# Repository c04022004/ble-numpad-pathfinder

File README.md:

# README.md

A pathfinder PCB for the upcoming Lipo-powered version of ESP32 BLE numpad. Arduino code also attached.

[Schematics PDF](./sch-export.pdf) | [Arduino Code](./arduino-freertos-code/ble_keyboard/ble_keyboard.ino) | [3D model](./3d-models/numpad-case-v10.3mf)

## Showcase

Assembled PCB  

</p>

Assembled PCB  w/ 3D print parts  

</p>

## 3D-printed Parts

The two 3D printed parts (front plate & base) are fixed to the PCB asembly with 2pcs M3x20 screws.  
The parts are designed in Fusion360, and the exported files can be found at the [3d-models/](./3d-models/) folder.

## Known Problems
- ~~USB Type-C CC pins was lay out incorrectly~~ (still testing, maybe a USB cable compat issue)
    - Reason: CC pins should be connected to `GND` with `5.1kΩ` resistor per USB Type-C definition ([link1](https://community.silabs.com/s/article/what-s-the-role-of-cc-pin-in-type-c-solution?language=en_US) [link2](https://community.silabs.com/s/article/legacy-usb-device-detection-by-type-c?language=en_US))
    - Temporary fix: not populating `R10` & `R11`, might led to inability to connect when Type-C plug is flipped
- WS2812 data line `DIN` might be affected my noise
    - Problem: Should add a `500Ω` resistor in series on `DIN` line to improve signal reliability, as per NeoPixel UberGuide
    - Temporary fix: avoid changing CPU frequency scaling on-the-fly, which may affect GPIO line conditions
- TCA8418 IC is not intended to be use with key matrix and diodes
    - Reason: originally designed for (pathfinding) swapping in diode and check the effect of ghosting
    - Temporary fix: populate diode components with `0805 0Ω` resistors
- Hotplug shoe for keyswitch is not strong enough to hold it in place
    - Reason: there is no faceplate to hold/align the keyswitches
    - Temporary fix: use 5-pin version of keyswitches for added stability, use hotglue if necessary
    - **NEW**: use a 3d printed positioning plate uploaded [here](./3d-models/)

Hopefully all issues can be fixed in the next revision to the PCB.

## Credits

I used & referenced a lot from the design from the other open-source projects.  
Here is the list of git repos:  

### KiCAD
- https://github.com/keebio/keebio-components
- https://github.com/keebio/Keebo-Parts.pretty
- https://github.com/perigoso/keyswitch-kicad-library
- https://github.com/ebastler/marbastlib
- https://github.com/AnthonyDiGirolamo/i2c-thumb-keyboard
- https://github.com/gorbachev/KiCad-SSD1306-0.91-OLED-4pin-128x32.pretty
- https://github.com/sparkfun/SparkFun-KiCad-Libraries
- https://github.com/Digi-Key/digikey-kicad-library

### Arduino/FreeRTOS
- https://github.com/kitesurfer1404/WS2812FX
- https://github.com/greiman/SSD1306Ascii
- https://github.com/adafruit/Adafruit_INA219
- https://github.com/adafruit/Adafruit_TCA8418
- https://github.com/espressif/arduino-esp32
- https://www.freertos.org/a00113.html

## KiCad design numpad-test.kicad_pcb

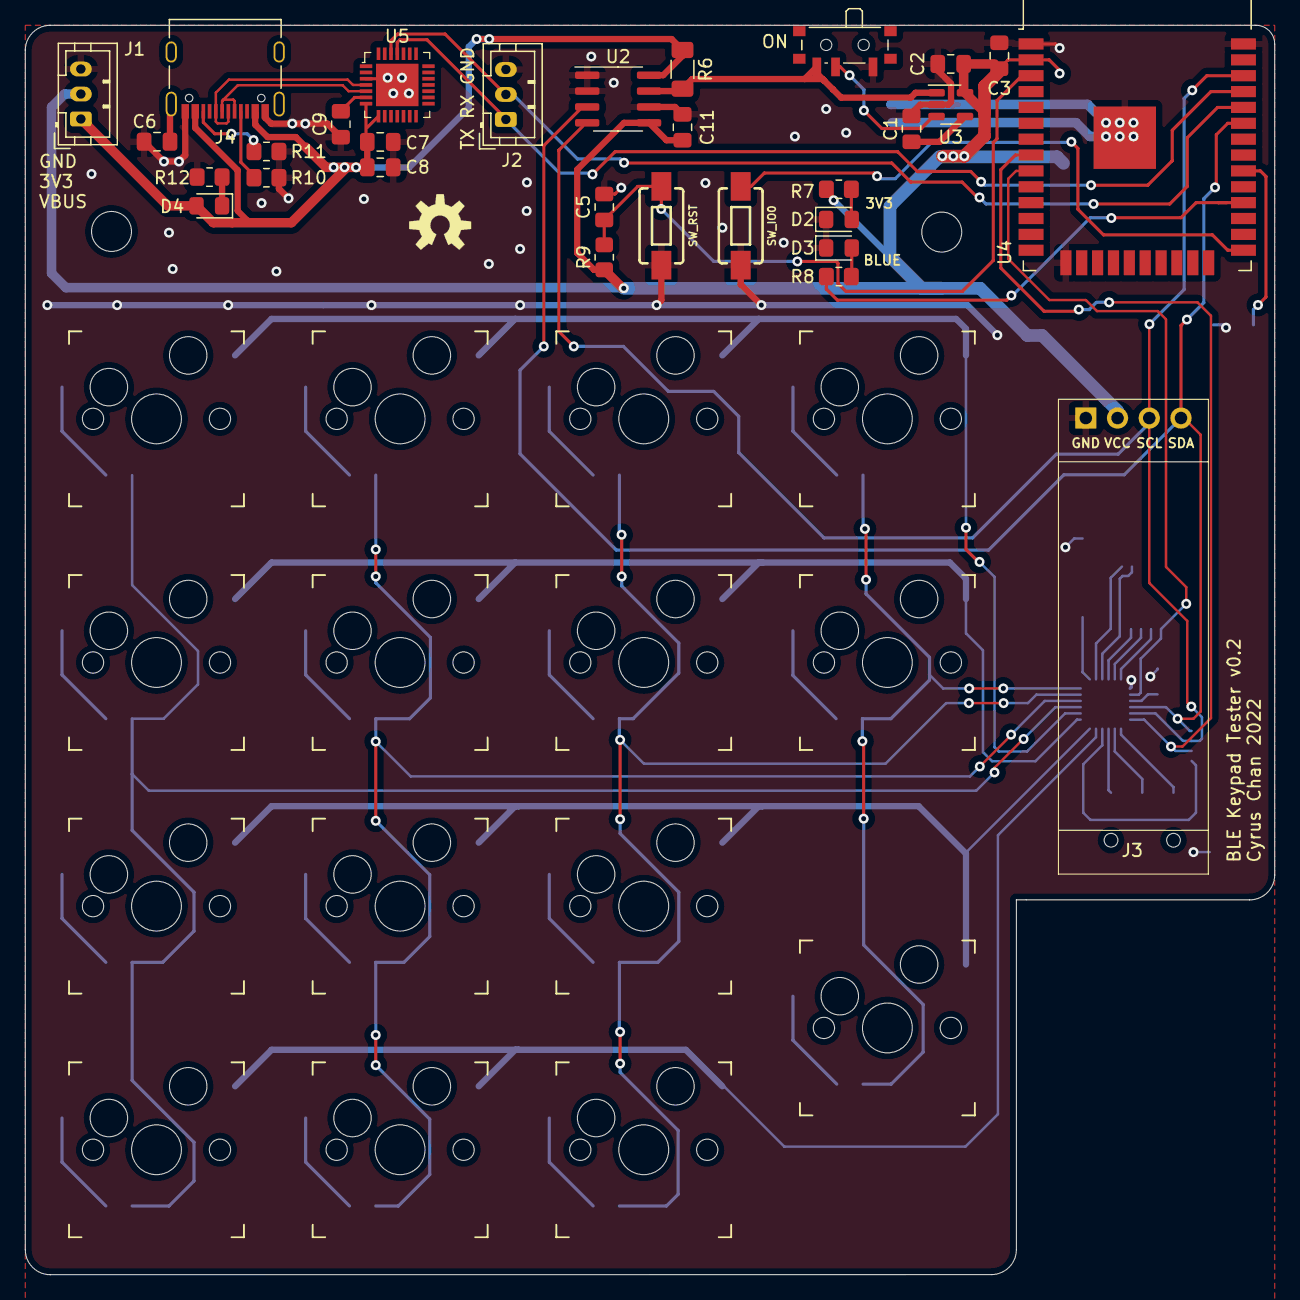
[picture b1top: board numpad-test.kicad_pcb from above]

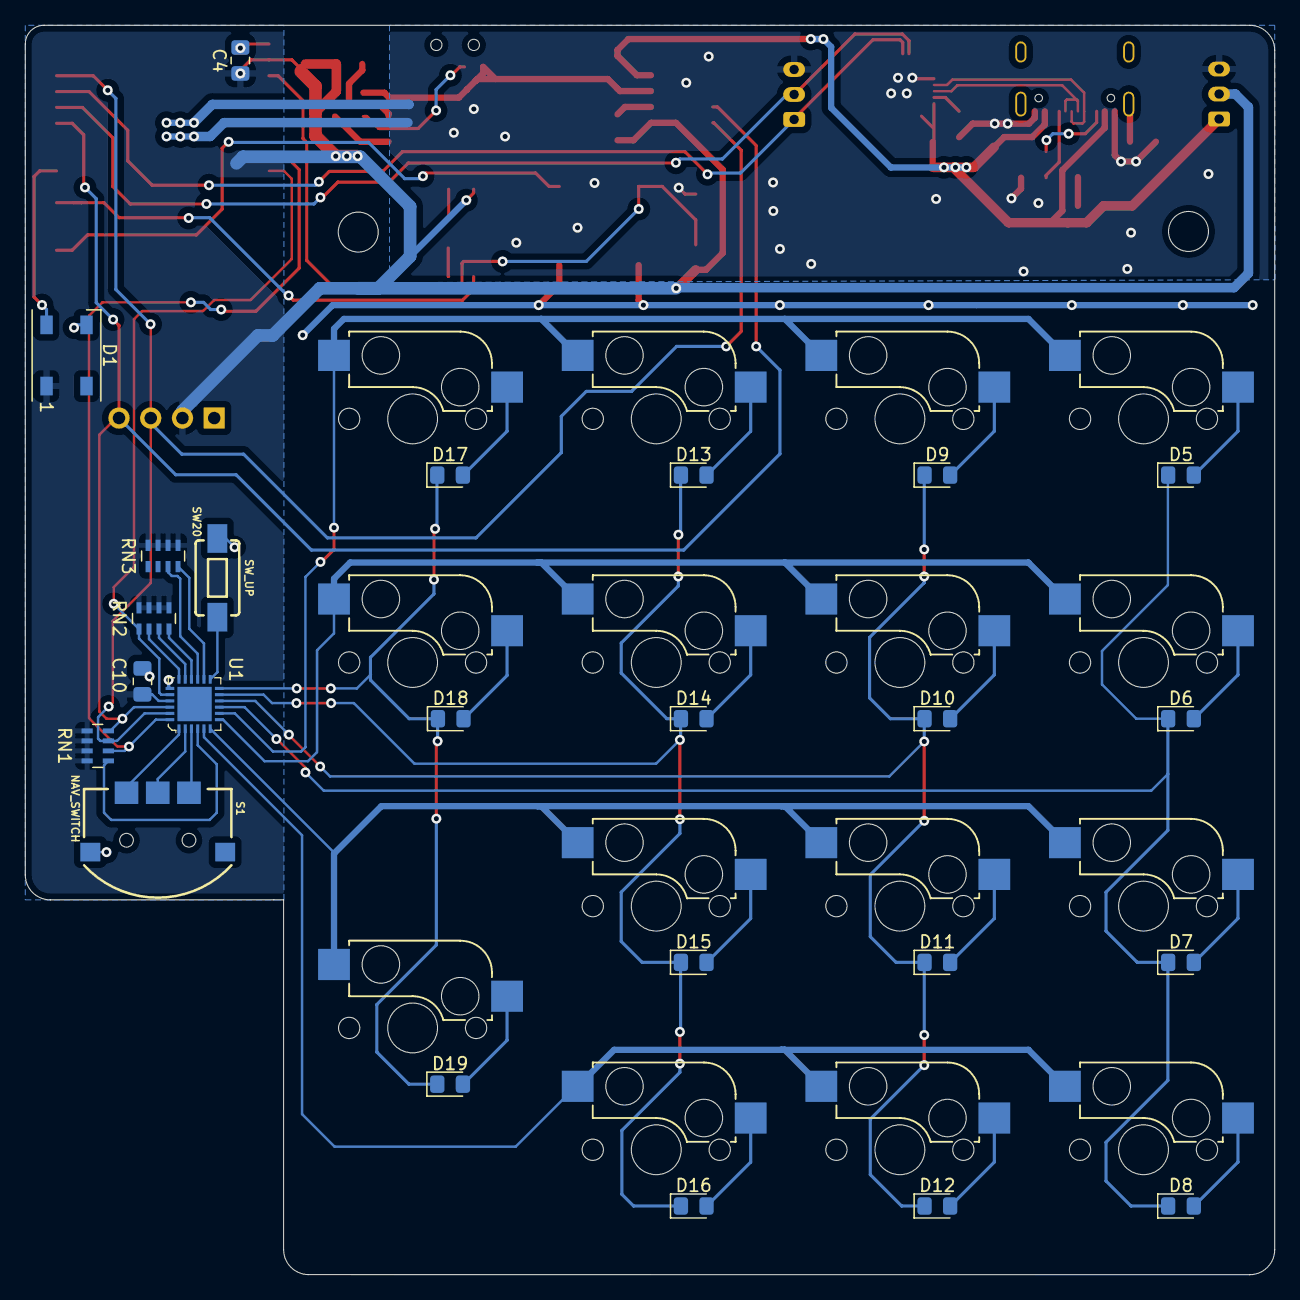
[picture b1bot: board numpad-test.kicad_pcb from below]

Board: 2 copper layers, 100.0 x 100.0 mm, 71 parts (24 on the bottom side), 58 nets.

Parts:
C1: 470p; C_0805_2012Metric_Pad1.18x1.45mm_HandSolder
C2: 2.2u; C_0805_2012Metric_Pad1.18x1.45mm_HandSolder
C3, C7, C9: 0.1u; C_0805_2012Metric_Pad1.18x1.45mm_HandSolder
C4: 10u; C_0805_2012Metric_Pad1.18x1.45mm_HandSolder
C5, C8, C10, C11: 1u; C_0805_2012Metric_Pad1.18x1.45mm_HandSolder
C6: 0.1uF; C_0805_2012Metric_Pad1.18x1.45mm_HandSolder
D1: WS2812B; LED_WS2812B_PLCC4_5.0x5.0mm_P3.2mm
D2: GREEN; LED_0805_2012Metric_Pad1.15x1.40mm_HandSolder
D3: BLUE; LED_0805_2012Metric_Pad1.15x1.40mm_HandSolder
D4: GREEN; D_0805_2012Metric_Pad1.15x1.40mm_HandSolder
D5, D6, D7, D8, D9, D10, D11, D12, D13, D14, D15, D16, D17, D18, D19: 1N4148; D_0805_2012Metric_Pad1.15x1.40mm_HandSolder
H1, H2: MountingHole; MountingHole_3.2mm_M3
J1, J2: Conn_01x03; JST_PH_B3B-PH-K_1x03_P2.00mm_Vertical
J3: Conn_OLED; SSD1306-0.91-OLED-4pin-128x32
J4: USB_C_Receptacle_USB2.0; USB_C_Receptacle_Palconn_UTC16-G
R6: R100; R_1206_3216Metric_Pad1.30x1.75mm_HandSolder
R7, R8: 3k; R_0805_2012Metric_Pad1.20x1.40mm_HandSolder
R9, R12: 10k; R_0805_2012Metric_Pad1.20x1.40mm_HandSolder
R10, R11: 5.1k; R_0805_2012Metric_Pad1.20x1.40mm_HandSolder
RN1, RN2, RN3: R_Pack04 10k; R_Array_Concave_4x0603
S1: NAV_SWITCH
SW1: SW_SPDT; SW_SPDT_PCM12
SW2: SW_RST; TACTILE_SWITCH_SMD_6.0X3.5MM
SW3: SW_IO0; TACTILE_SWITCH_SMD_6.0X3.5MM
SW4, SW5, SW6, SW7, SW8, SW9, SW10, SW11, SW12, SW13, SW14, SW15, SW16, SW17, SW18: SW_Push_45deg; Kailh_socket_MX
SW20: SW_UP; TACTILE_SWITCH_SMD_6.0X3.5MM
U1: TCA8418-teensy32; WQFN-24-1EP_4x4mm
U2: INA219AxD; SOIC-8_3.9x4.9mm_P1.27mm
U3: MIC5219-3.3YM5; SOT-23-5
U4: ESP32-WROOM-32
U5: CP2102-GMR_NRND; VFQFN-28-1EP_5x5mm

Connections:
+3.3V: C2.1, C3.1, C4.1, C10.1, C11.1, D1.1 (VDD), J1.2, J3.2, R7.2, R9.1, RN1.1 (R1.1), RN1.2 (R2.1), RN1.3 (R3.1), RN1.4 (R4.1), RN2.1 (R1.1), RN2.2 (R2.1), RN2.3 (R3.1), RN2.4 (R4.1), RN3.1 (R1.1), RN3.2 (R2.1), RN3.3 (R3.1), RN3.4 (R4.1), U1.21 (VCC), U2.5 (VS), U3.5 (OUT), U4.2 (VDD)
/TYPE-C CP2102 UART/TYPEC_D+: J4.A6 (D+), J4.B6 (D+), U5.4 (D+)
/TYPE-C CP2102 UART/TYPEC_D-: J4.A7 (D-), J4.B7 (D-), U5.5 (D-)
BTN1: S1.1, U1.3 (ROW5)
BTN2: S1.2, U1.1 (ROW7)
BTNT: S1.T, U1.2 (ROW6)
COL0: D5.1 (K), D6.1 (K), D7.1 (K), D8.1 (K), U1.9 (COL0)
COL1: D9.1 (K), D10.1 (K), D11.1 (K), D12.1 (K), U1.10 (COL1)
COL2: D13.1 (K), D14.1 (K), D15.1 (K), D16.1 (K), U1.11 (COL2)
COL3: D17.1 (K), D18.1 (K), D19.1 (K), U1.12 (COL3)
COL5_NC: RN3.8 (R1.2), U1.14 (COL5)
COL6_NC: RN3.7 (R2.2), U1.15 (COL6)
COL7_NC: RN2.8 (R1.2), U1.16 (COL7)
COL8_NC: RN2.7 (R2.2), U1.17 (COL8)
COL9_NC: RN2.6 (R3.2), U1.18 (COL9)
GND: C1.2, C2.2, C3.2, C4.2, C5.2, C6.1, C7.2, C8.2, C9.1, C10.2, C11.2, D1.3 (VSS), D2.1 (K), D3.1 (K), J1.3, J2.3, J3.1, J4.A1 (GND), J4.A12 (GND), J4.B1 (GND), J4.B12 (GND), R10.2, R11.1, R12.2, S1.C, SW1.1 (A), SW2.1, SW3.2, SW20.2, U1.19 (GND), U2.1 (A1), U2.2 (A0), U2.6 (GND), U3.2 (GND), U4.1 (GND), U4.15 (GND), U4.38 (GND), U4.39 (GND), U5.3 (GND), U5.29 (GND_PAD)
I2C_SCL: J3.3, RN1.7 (R2.2), U1.23 (SCL), U2.4 (SCL), U4.36 (IO22)
I2C_SDA: J3.4, RN1.8 (R1.2), U1.22 (SDA), U2.3 (SDA), U4.33 (IO21)
IO0: SW3.1, U4.25 (IO0)
KEY_INT: RN1.6 (R3.2), U1.24 (INT), U4.8 (IO32)
KEY_RST: RN2.5 (R4.2), U1.20 (RESET), U4.9 (IO33)
LDO_IN+: C7.1, C8.1, D4.2 (A), J1.1, J4.A4 (VBUS), J4.A9 (VBUS), J4.B4 (VBUS), J4.B9 (VBUS), R6.1, U2.8 (IN+), U5.7 (REGIN), U5.8 (VBUS)
LDO_IN-: R6.2, SW1.3 (C), U2.7 (IN-), U3.1 (IN)
LED_BLUE: R8.2, U4.28 (IO17)
LED_WS: D1.4 (DIN), U4.30 (IO18)
unnamed: C1.1, U3.4 (BP)
unnamed: C6.2, J4.S1 (SHIELD)
unnamed: C9.2, U5.6 (VDD)
unnamed: D2.2 (A), R7.1
unnamed: D3.2 (A), R8.1
unnamed: D4.1 (K), R12.1
unnamed: D5.2 (A), SW4.2
unnamed: D6.2 (A), SW5.2
unnamed: D7.2 (A), SW6.2
unnamed: D8.2 (A), SW7.2
unnamed: D9.2 (A), SW8.2
unnamed: D10.2 (A), SW9.2
unnamed: D11.2 (A), SW10.2
unnamed: D12.2 (A), SW11.2
unnamed: D13.2 (A), SW12.2
unnamed: D14.2 (A), SW13.2
unnamed: D15.2 (A), SW14.2
unnamed: D16.2 (A), SW15.2
unnamed: D17.2 (A), SW16.2
unnamed: D18.2 (A), SW17.2
unnamed: D19.2 (A), SW18.2
unnamed: J4.A5 (CC1), R10.1
unnamed: J4.B5 (CC2), R11.2
unnamed: SW1.2 (B), U3.3 (EN)
ROW0: SW4.1, SW8.1, SW12.1, SW16.1, U1.8 (ROW0)
ROW1: SW5.1, SW9.1, SW13.1, SW17.1, U1.7 (ROW1)
ROW2: SW6.1, SW10.1, SW14.1, SW18.1, U1.6 (ROW2)
ROW3: SW7.1, SW11.1, SW15.1, U1.5 (ROW3)
ROW4_NC: RN1.5 (R4.2), U1.4 (ROW4)
RST: C5.1, R9.2, SW2.2, U4.3 (EN)
RXD: J2.2, U4.34 (RXD0/IO3), U5.26 (TXD)
SW_UP: SW20.1, U1.13 (COL4)
TXD: J2.1, U4.35 (TXD0/IO1), U5.25 (RXD)

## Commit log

2022-10-30 <bulk> Inital Upload
2022-10-30 <docs> Add readme content, remove bak files
2022-10-30 <docs> Update README links
2022-10-31 <docs> Add README known problems section
2022-11-02 <chore> remove anime silkscreen & gerber
2022-11-02 <docs> update README
2023-06-29 <docs> Update README with pics for 3d-printed parts
2023-06-29 <docs> Upload 3d models for final assembly
2023-06-29 <docs> Align static image with 3d model
